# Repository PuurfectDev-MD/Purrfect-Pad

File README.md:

# Purrfect-Pad
A hackclub project Submission
A minimalist - cool looking (allegedly) macropad for cat lovers and productive people.

## Features
* **Custom 4-Key Mechanical Layout:** 
* **Integrated OLED Display:** 128x32 screen for status and animations
* **Cool Asthetic** People fond of cats need a paw on their desk all the time!
* **Rotary Encoder:** Precision control for volume 
* **XIAO RP2040 Powered:** Compact and powerful processing

## Schematic

## PCB

## 3D Model Case

## BOM 
* 1x Seeed Studio XIAO RP2040
* 1x 0.91" SSD1306 OLED Display (128x32)
* 4x Mechanical Switches 
* 1x Rotary Encoder
* 4x M3 x 16mm Socket Head Cap Screws
* 3D Printed Case

## Note
Making the pawpad was awsome. Always wanted to get into 3d modelling and making something tangable instead of my projects just being a concept. Wasnt execting to take as much time it took to finish the pawpad completly. I learned a lot of Fusion 360 and PCB designing :> looks like Ill be making more of my projects tangible.

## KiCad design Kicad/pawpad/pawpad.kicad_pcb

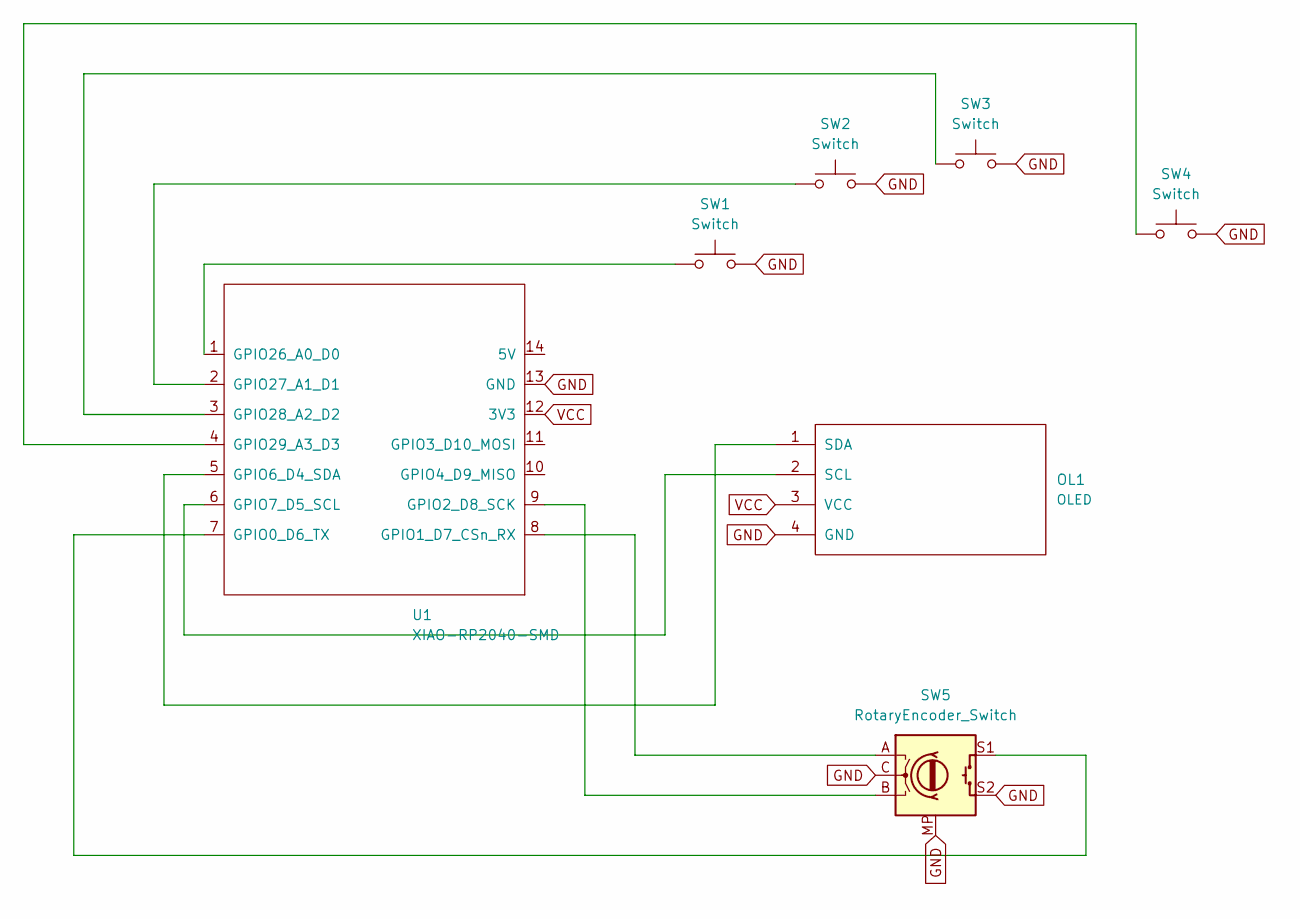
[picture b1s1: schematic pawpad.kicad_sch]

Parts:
OL1: OLED; OLED_128x32
SW1, SW2, SW3, SW4: Switch; MX_PCB_1.00u
SW5: RotaryEncoder_Switch; RotaryEncoder_Alps_EC11E_Vertical_H20mm
U1: XIAO-RP2040-SMD; Seeed_XIAO_RP2040

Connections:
GND: OL1.4 (GND), SW1.2, SW2.2, SW3.2, SW4.2, SW5.C, SW5.MP, SW5.S2, U1.13 (GND)
unnamed: OL1.2 (SCL), U1.6 (GPIO7_D5_SCL)
unnamed: OL1.1 (SDA), U1.5 (GPIO6_D4_SDA)
unnamed: SW5.S1, U1.7 (GPIO0_D6_TX)
unnamed: SW5.A, U1.8 (GPIO1_D7_CSn_RX)
unnamed: SW5.B, U1.9 (GPIO2_D8_SCK)
unnamed: SW1.1, U1.1 (GPIO26_A0_D0)
unnamed: SW2.1, U1.2 (GPIO27_A1_D1)
unnamed: SW3.1, U1.3 (GPIO28_A2_D2)
unnamed: SW4.1, U1.4 (GPIO29_A3_D3)
VCC: OL1.3 (VCC), U1.12 (3V3)

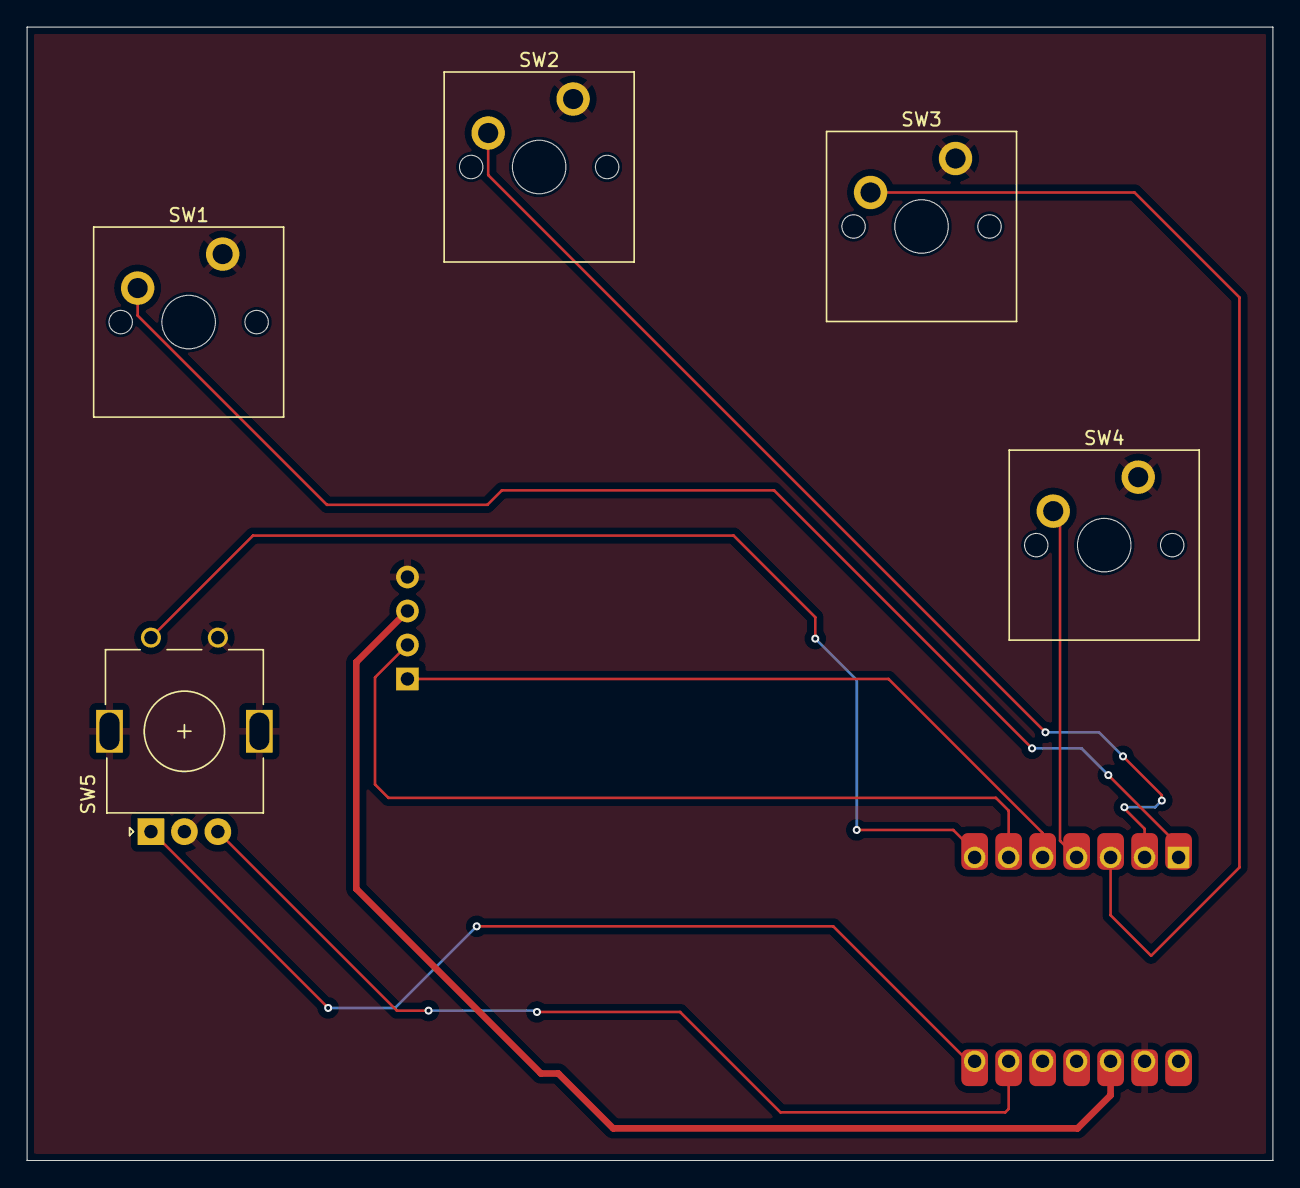
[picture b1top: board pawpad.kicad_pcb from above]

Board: 2 copper layers, 93.1 x 84.7 mm, 7 parts (0 on the bottom side), 11 nets.

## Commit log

2026-01-19 Finised v2
2026-01-19 Edited Readme
2026-01-19 README fix
